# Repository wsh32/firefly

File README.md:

# Firefly: Mini coordinated drone shows

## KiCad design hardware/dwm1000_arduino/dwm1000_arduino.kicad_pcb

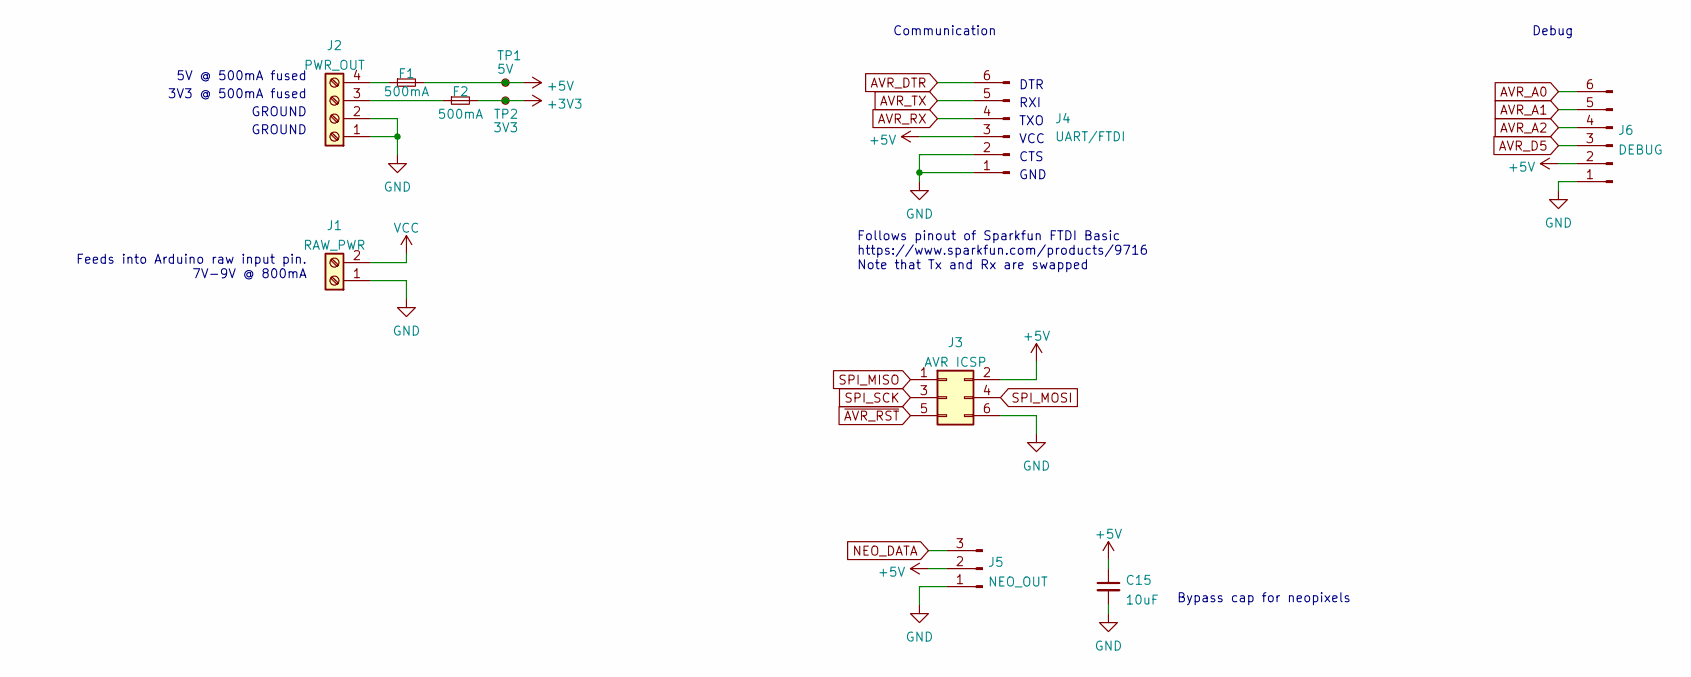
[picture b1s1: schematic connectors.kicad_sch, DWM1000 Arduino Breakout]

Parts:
C15: 10uF; C_0805_2012Metric_Pad1.18x1.45mm_HandSolder; DigiKey 445-12654-6-ND
F1, F2: 500mA; Fuse_1206_3216Metric_Pad1.42x1.75mm_HandSolder; DigiKey 507-1802-6-ND
J1: RAW_PWR; TerminalBlock_Phoenix_PT-1,5-2-3.5-H_1x02_P3.50mm_Horizontal; DigiKey 277-15481-ND
J2: PWR_OUT; TerminalBlock_Phoenix_PT-1,5-4-3.5-H_1x04_P3.50mm_Horizontal; DigiKey 277-1860-ND
J3: AVR ICSP; PinHeader_2x03_P2.54mm_Vertical
J4: UART/FTDI; PinHeader_1x06_P2.54mm_Vertical
J5: NEO_OUT; PinHeader_1x03_P2.54mm_Vertical
J6: DEBUG; PinHeader_1x06_P2.54mm_Vertical
TP1: 5V; TestPoint_Pad_D1.0mm
TP2: 3V3; TestPoint_Pad_D1.0mm

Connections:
+3V3: F2.2, TP2.1; also elsewhere on the board
+5V: C15.1, F1.2, J3.2, J4.3, J5.2, J6.2, TP1.1; also elsewhere on the board
AVR_A0: J6.6; also elsewhere on the board
AVR_A1: J6.5; also elsewhere on the board
AVR_A2: J6.4; also elsewhere on the board
AVR_D5: J6.3; also elsewhere on the board
GND: C15.2, J1.1, J2.1, J2.2, J3.6, J4.1, J4.2, J5.1, J6.1; also elsewhere on the board
unnamed: F1.1, J2.4
unnamed: F2.1, J2.3
SPI_MISO: J3.1; also elsewhere on the board
SPI_MOSI: J3.4; also elsewhere on the board
SPI_SCK: J3.3
VCC: J1.2; also elsewhere on the board
~AVR_RST: J3.5; also elsewhere on the board

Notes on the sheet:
GND
Bypass cap for neopixels
GROUND
DTR
Feeds into Arduino raw input pin. 7V-9V @ 800mA
5V @ 500mA fused
Communication
TXO
CTS
RXI
Follows pinout of Sparkfun FTDI Basic https://www.sparkfun.com/products/9716 Note that Tx and Rx are swapped
3V3 @ 500mA fused
Debug
VCC

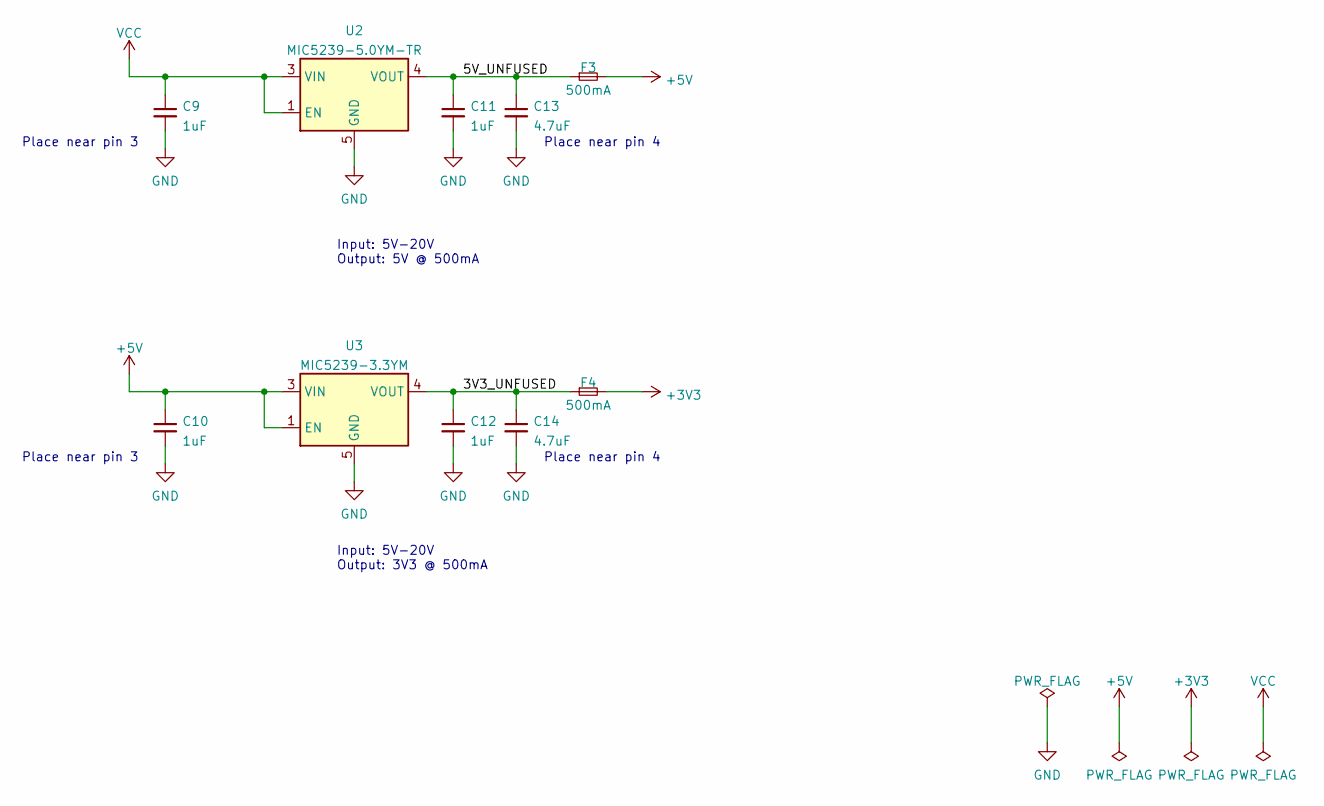
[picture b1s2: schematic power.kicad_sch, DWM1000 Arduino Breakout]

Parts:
C9, C10, C11, C12: 1uF; C_0805_2012Metric_Pad1.18x1.45mm_HandSolder; DigiKey 478-08055C105JAT2ACT-ND
C13, C14: 4.7uF; C_0805_2012Metric_Pad1.18x1.45mm_HandSolder; DigiKey 1276-6722-1-ND
F3, F4: 500mA; Fuse_1206_3216Metric_Pad1.42x1.75mm_HandSolder; DigiKey 507-1802-6-ND
U2: MIC5239-5.0YM-TR; SOIC-8_3.9x4.9mm_P1.27mm; DigiKey MIC5239-5.0YM-CT-ND
U3: MIC5239-3.3YM; SOIC-8_3.9x4.9mm_P1.27mm; DigiKey 576-2394-ND

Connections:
+3V3: F4.2; also elsewhere on the board
+5V: C10.1, F3.2, U3.1 (EN), U3.3 (VIN); also elsewhere on the board
/Power/3V3_UNFUSED: C12.1, C14.1, F4.1, U3.4 (VOUT)
/Power/5V_UNFUSED: C11.1, C13.1, F3.1, U2.4 (VOUT)
GND: C9.2, C10.2, C11.2, C12.2, C13.2, C14.2, U2.5 (GND), U2.6 (GND), U2.7 (GND), U2.8 (GND), U3.5 (GND), U3.6 (GND), U3.7 (GND), U3.8 (GND); also elsewhere on the board
VCC: C9.1, U2.1 (EN), U2.3 (VIN); also elsewhere on the board

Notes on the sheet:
Input: 5V-20V Output: 3V3 @ 500mA
Input: 5V-20V Output: 5V @ 500mA
Place near pin 3
Place near pin 4

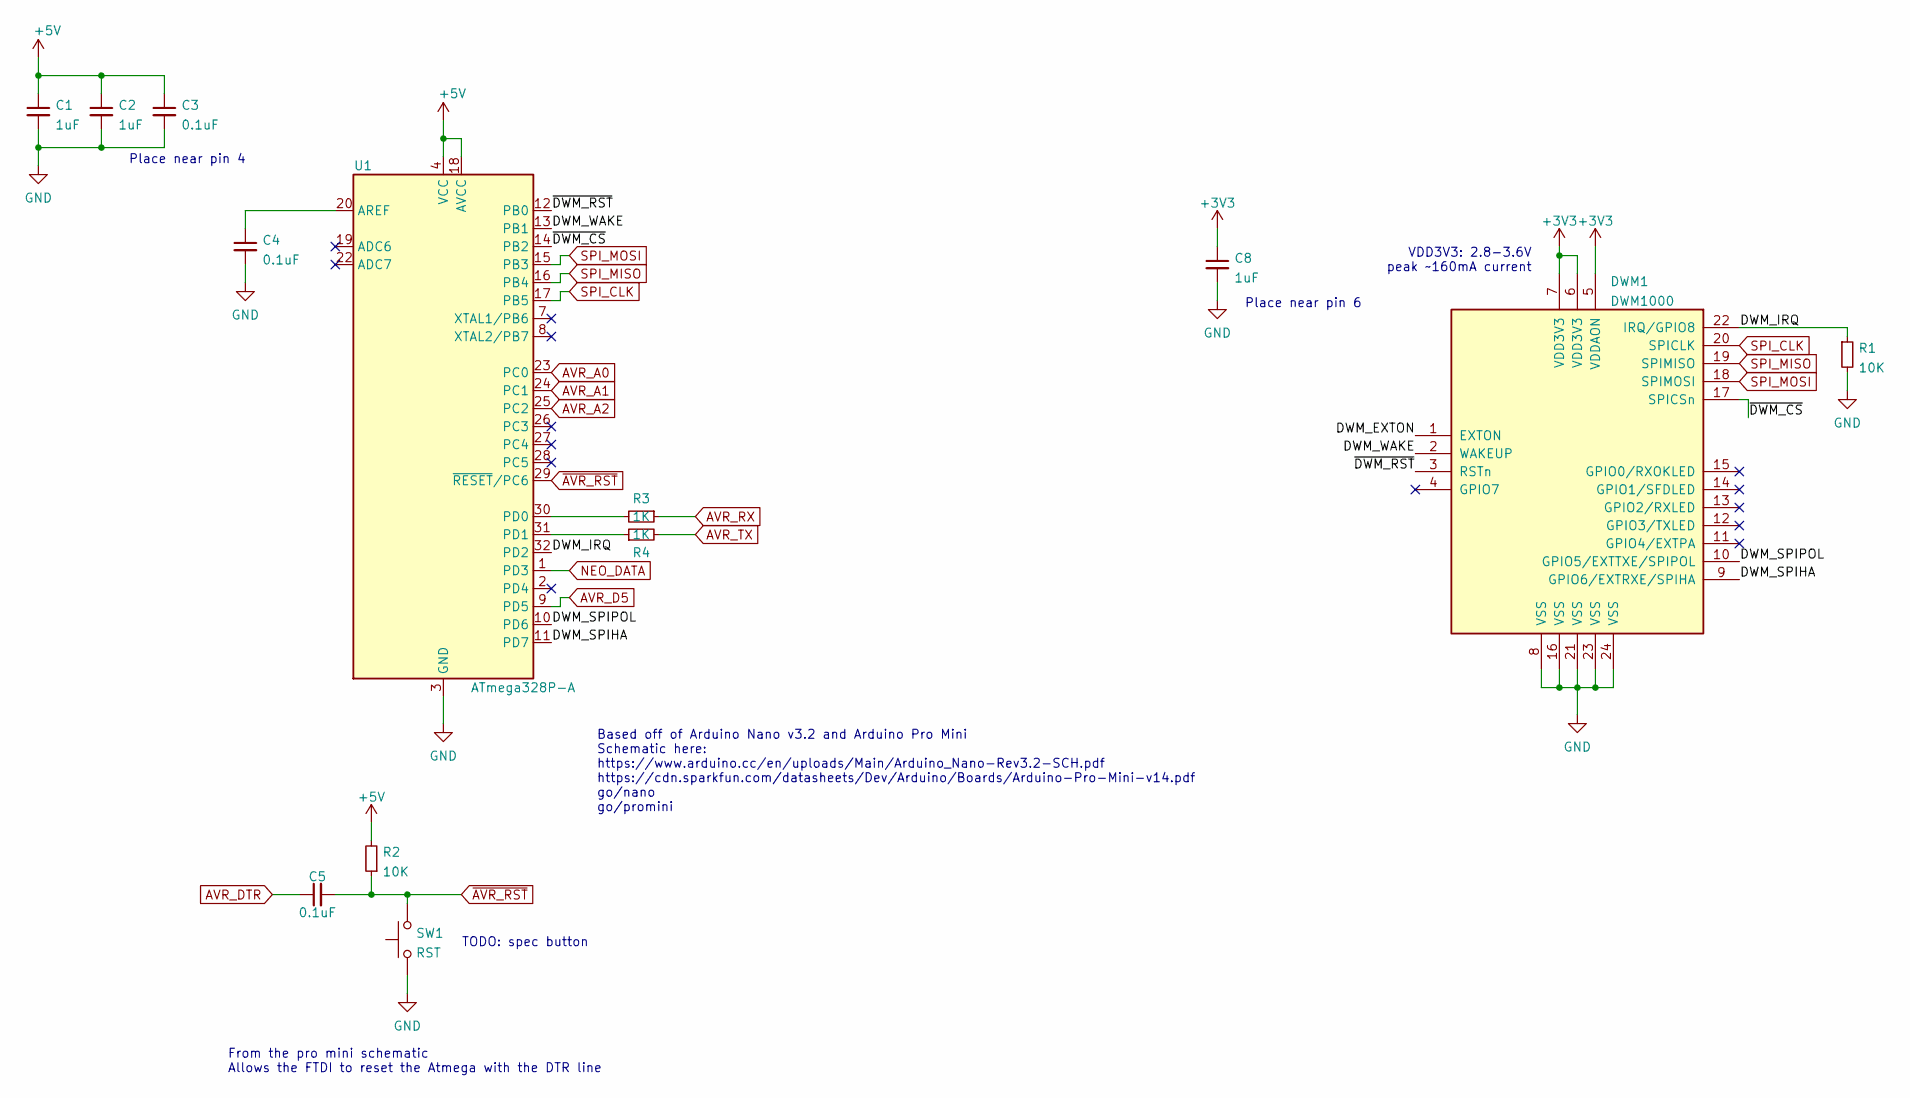
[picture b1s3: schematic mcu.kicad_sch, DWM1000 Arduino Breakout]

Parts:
C1, C2, C8: 1uF; C_0805_2012Metric_Pad1.18x1.45mm_HandSolder; DigiKey 478-08055C105JAT2ACT-ND
C3, C4, C5: 0.1uF; C_0805_2012Metric_Pad1.18x1.45mm_HandSolder; DigiKey 587-1133-1-ND
DWM1: DWM1000
R1: 10K; R_0805_2012Metric_Pad1.20x1.40mm_HandSolder; DigiKey RMCF0805JT10K0DKR-ND
R2: 10K; R_0805_2012Metric_Pad1.20x1.40mm_HandSolder; DigiKey RMCF0805JT10K0CT-ND
R3, R4: 1K; R_0805_2012Metric_Pad1.20x1.40mm_HandSolder; DigiKey RMCF0805FT1K00CT-ND
SW1: RST; SW_PUSH_6mm; DigiKey CKN12307-ND
U1: ATmega328P-A; TQFP-32_7x7mm_P0.8mm

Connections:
+3V3: C8.1, DWM1.5 (VDDAON), DWM1.6 (VDD3V3), DWM1.7 (VDD3V3); also elsewhere on the board
+5V: C1.1, C2.1, C3.1, R2.2, U1.4 (VCC), U1.6 (VCC), U1.18 (AVCC); also elsewhere on the board
/MCUs/DWM_EXTON: DWM1.1 (EXTON)
/MCUs/DWM_IRQ: DWM1.22 (IRQ/GPIO8), R1.1, U1.32 (PD2)
/MCUs/DWM_SPIHA: DWM1.9 (GPIO6/EXTRXE/SPIHA), U1.11 (PD7)
/MCUs/DWM_SPIPOL: DWM1.10 (GPIO5/EXTTXE/SPIPOL), U1.10 (PD6)
/MCUs/DWM_WAKE: DWM1.2 (WAKEUP), U1.13 (PB1)
/MCUs/~DWM_CS: DWM1.17 (SPICSn), U1.14 (PB2)
/MCUs/~DWM_RST: DWM1.3 (RSTn), U1.12 (PB0)
AVR_A0: U1.23 (PC0); also elsewhere on the board
AVR_A1: U1.24 (PC1); also elsewhere on the board
AVR_A2: U1.25 (PC2); also elsewhere on the board
AVR_D5: U1.9 (PD5); also elsewhere on the board
AVR_DTR: C5.1; also elsewhere on the board
AVR_RX: R3.1; also elsewhere on the board
AVR_TX: R4.2; also elsewhere on the board
GND: C1.2, C2.2, C3.2, C4.2, C8.2, DWM1.8 (VSS), DWM1.16 (VSS), DWM1.21 (VSS), DWM1.23 (VSS), DWM1.24 (VSS), R1.2, SW1.1, U1.3 (GND), U1.5 (GND), U1.21 (GND); also elsewhere on the board
NEO_DATA: U1.1 (PD3); also elsewhere on the board
unnamed: C4.1, U1.20 (AREF)
unnamed: R3.2, U1.30 (PD0)
unnamed: R4.1, U1.31 (PD1)
SPI_CLK: DWM1.20 (SPICLK), U1.17 (PB5)
SPI_MISO: DWM1.19 (SPIMISO), U1.16 (PB4); also elsewhere on the board
SPI_MOSI: DWM1.18 (SPIMOSI), U1.15 (PB3); also elsewhere on the board
~AVR_RST: C5.2, R2.1, SW1.2, U1.29 (~RESET/PC6); also elsewhere on the board

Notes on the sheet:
Place near pin 6
VDD3V3: 2.8-3.6V peak ~160mA current
From the pro mini schematic Allows the FTDI to reset the Atmega with the DTR line
Place near pin 4
Based off of Arduino Nano v3.2 and Arduino Pro Mini Schematic here: https://www.arduino.cc/en/uploads/Main/Arduino_Nano-Rev3.2-SCH.pdf https://cdn.sparkfun.com/datasheets/Dev/Arduino/Boards/Arduino-Pro-Mini-v14.pdf go/nano go/promini
TODO: spec button

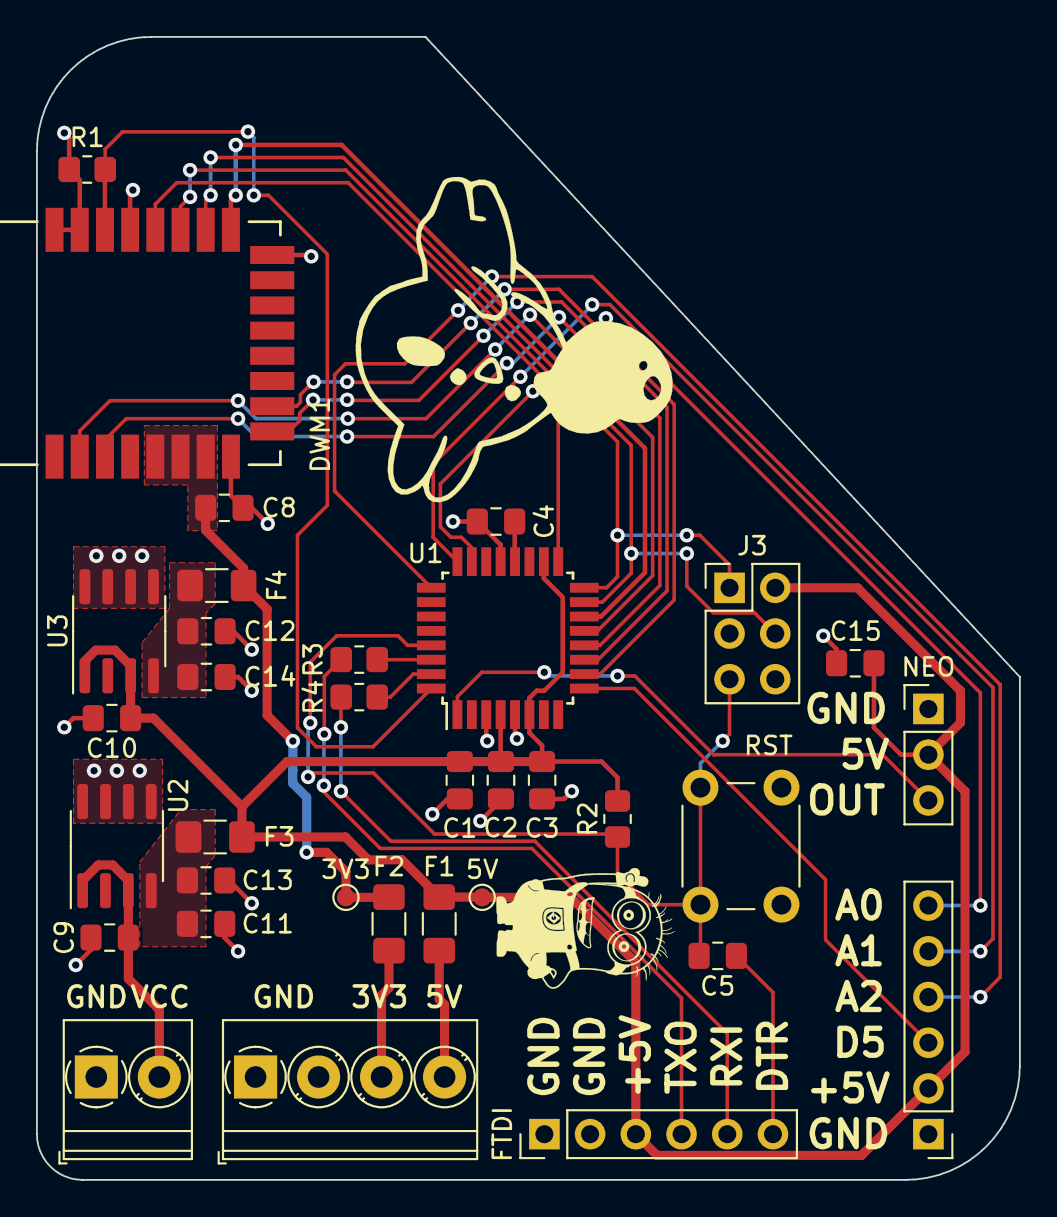
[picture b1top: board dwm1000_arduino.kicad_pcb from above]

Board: 2 copper layers, 54.6 x 63.5 mm, 34 parts (0 on the bottom side), 29 nets.

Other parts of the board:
FTDI: UART/FTDI; PinHeader_1x06_P2.54mm_Vertical
NEO: NEO_OUT; PinHeader_1x03_P2.54mm_Vertical
RST: RST; SW_PUSH_6mm

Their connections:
+5V: FTDI.3, NEO.2; also elsewhere on the board
AVR_DTR: FTDI.6; also elsewhere on the board
AVR_RX: FTDI.4; also elsewhere on the board
AVR_TX: FTDI.5; also elsewhere on the board
GND: FTDI.1, FTDI.2, NEO.1, RST.1; also elsewhere on the board
NEO_DATA: NEO.3; also elsewhere on the board
~AVR_RST: RST.2; also elsewhere on the board

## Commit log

2022-01-22 add gitignore
2022-01-28 initialize repo structure
2022-02-12 first rev dwm1000 schematic
2022-02-13 finixh schematic and first pass layout
2022-02-13 update schematic pdf
2022-02-14 fix ground plane, fix connector placement, add silkscreen
2022-02-15 add gerbers to gitignore
2022-02-15 remove silkscreen refs for the mounting holes
2022-03-28 add libraries
2022-04-01 anchor and tag arduino firmware
2022-04-03 start rev 2 of the dwm board
2022-04-08 rev 2 pcb schematic
2022-04-11 finish layout
2022-04-11 update pdf
